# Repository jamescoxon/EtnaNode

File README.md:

# EtnaNode
Solar powered UKHASnet node

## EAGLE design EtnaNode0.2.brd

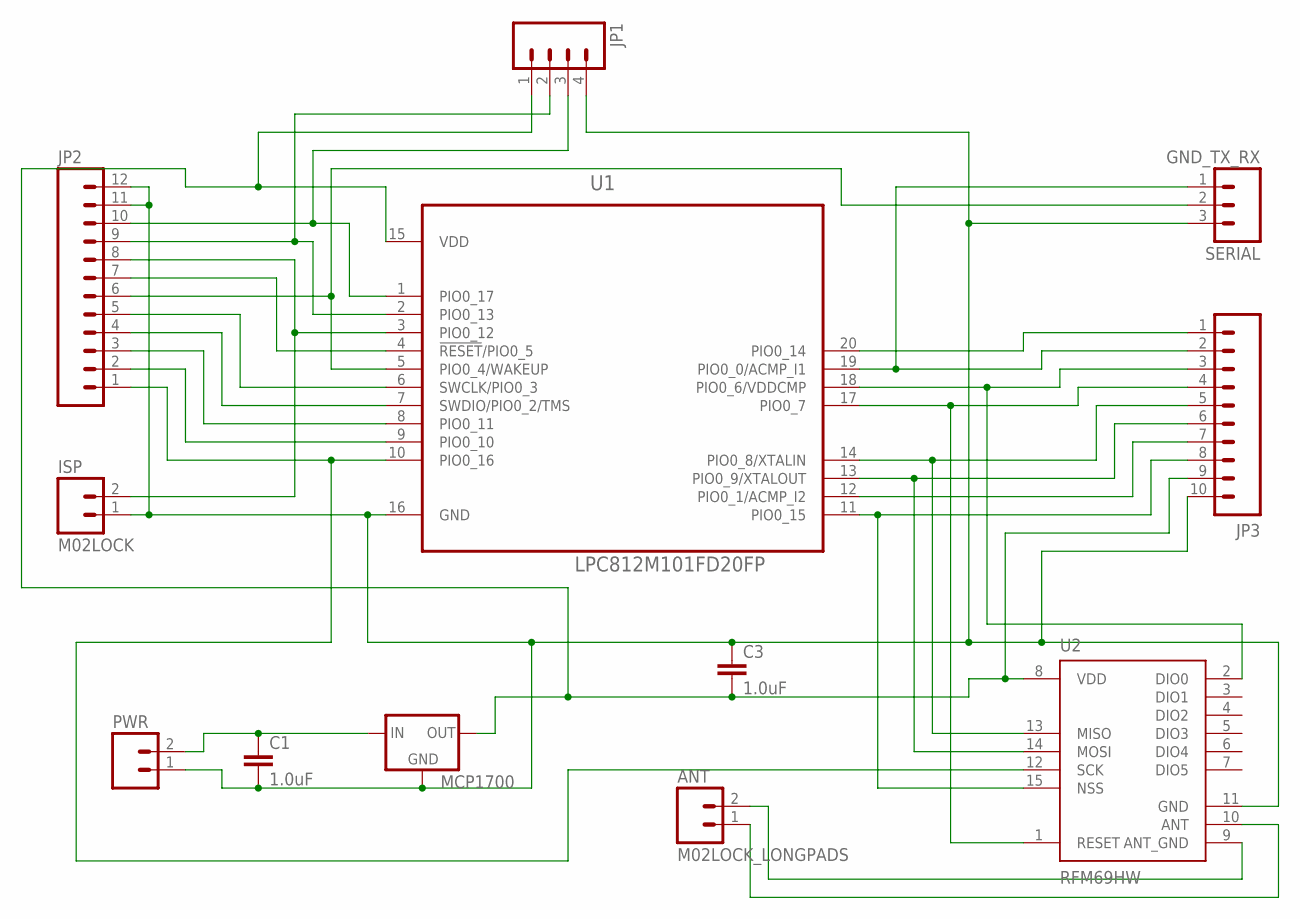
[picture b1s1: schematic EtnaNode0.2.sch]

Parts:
ANT: M02LOCK_LONGPADS; 1X02_LOCK_LONGPADS
C1, C3: 1.0uF; CAP-PTH-SMALL
ISP: M02LOCK; 1X02_LOCK
JP1: M04LOCK; 1X04_LOCK
JP2: M12LOCK; 1X12_LOCK
JP3: M10LOCK; 1X10_LOCK
MCP1700: MCP1700INLINE; TO92-INLINE
PWR: M02LOCK_LONGPADS; 1X02_LOCK_LONGPADS
SERIAL: GND_TX_RX; 1X03_LOCK
U1: LPC812M101FD20FP; SOIC127P1032X265-20N
U2: RFM69HW; RFM69W-XXXS2

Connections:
ANT_GND: ANT.2, U2.9 (ANT_GND)
GND: C1.2, C3.1, ISP.1, JP1.4, JP2.11, JP2.12 (VCC), JP3.10, MCP1700.1 (GND), PWR.1, SERIAL.3 (U0_RXD), U1.16 (GND), U2.11 (GND)
unnamed: C1.1, MCP1700.2 (IN), PWR.2
unnamed: JP3.2, SERIAL.1 (GND), U1.19 (PIO0_0/ACMP_I1)
unnamed: JP2.6, SERIAL.2 (U0_TXD), U1.5 (PIO0_4/WAKEUP)
unnamed: ISP.2, JP2.8, U1.3 (PIO0_12)
unnamed: JP3.5, U1.14 (PIO0_8/XTALIN), U2.13 (MISO)
unnamed: JP3.6, U1.13 (PIO0_9/XTALOUT), U2.14 (MOSI)
unnamed: JP3.7, U1.12 (PIO0_1/ACMP_I2)
unnamed: JP3.8, U1.11 (PIO0_15), U2.15 (NSS)
unnamed: JP3.4, U1.17 (PIO0_7), U2.1 (RESET)
unnamed: JP3.3, U1.18 (PIO0_6/VDDCMP), U2.2 (DIO0)
unnamed: JP2.2, U1.9 (PIO0_10)
unnamed: JP2.3, U1.8 (PIO0_11)
unnamed: JP2.4, U1.7 (SWDIO/PIO0_2/TMS)
unnamed: JP2.5, U1.6 (SWCLK/PIO0_3)
unnamed: JP2.7, U1.4 (!RESET!/PIO0_5)
unnamed: JP1.2, JP2.9, U1.2 (PIO0_13)
unnamed: JP1.3, JP2.10, U1.1 (PIO0_17)
unnamed: JP3.1, U1.20 (PIO0_14)
unnamed: ANT.1, U2.10 (ANT)
unnamed: JP2.1, U1.10 (PIO0_16), U2.12 (SCK)
VDD: C3.2, JP1.1, JP3.9, MCP1700.3 (OUT), U1.15 (VDD), U2.8 (VDD)

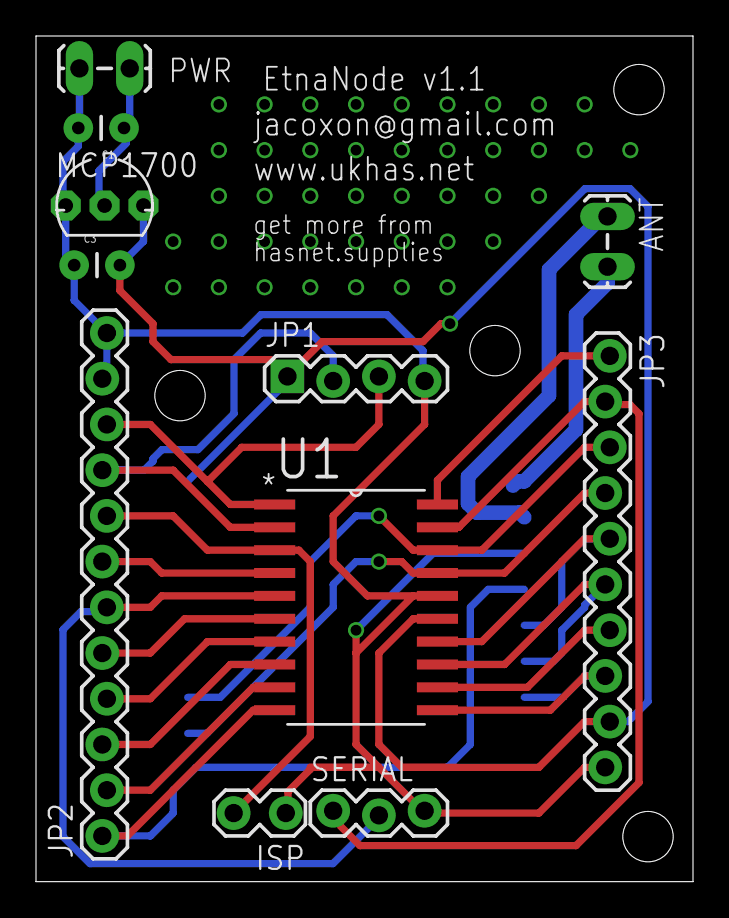
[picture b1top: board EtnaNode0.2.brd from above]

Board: 2 copper layers, 36.5 x 47.0 mm, 12 parts (1 on the bottom side), 23 nets.

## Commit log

2015-06-12 Create BOM
2015-06-12 Added diodes to BOM
2015-06-12 Update BOM
2015-06-19 added design files for EtnaNode PCB
2015-06-19 Create Development_Costs
2015-06-21 added stl
2015-11-11 added version 2 of Etnanode including second set of pins for GPS, switched to using MCP1700 for power supply, reduced size of pin holes and moved isp and serial closer together. On RFM69 moved 1 line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

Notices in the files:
parts and their libraries:
SparkFun-Connectors: Licensing: Creative Commons ShareAlike 4.0 International - https://creativecommons.org/licenses/by-sa/4.0
